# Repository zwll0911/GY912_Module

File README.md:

# 🚁 Industrial AHRS Navigation Module (V5.5)

> **High-Precision Navigation Core for Competition Robotics**

The **Industrial AHRS Navigation Module** is a robust sensor fusion engine built on the **ESP32-S3**. It delivers stable 6-axis orientation (Yaw, Pitch, Roll) via **1 Mbps CAN Bus** and offers **Dual-Mode Telemetry** (USB Serial + Wireless UDP) for real-time monitoring.

---

## 📑 Table of Contents

- [Key Features](#-key-features)
- [System Architecture Overview](#-system-architecture-overview)
- [Sensor Fusion Pipeline (ICM-20948 DMP)](#-sensor-fusion-pipeline-icm-20948-dmp)
- [System Status Indicators](#-system-status-indicators)
- [FreeRTOS Task Architecture](#freertos-task-architecture)
- [Hardware Specifications](#️-hardware-specifications)
- [Quick Start](#-quick-start)
- [Documentation](#-documentation)
- [Project Structure](#-project-structure)

---

## 🚀 Key Features

| Feature | Detail |
| :--- | :--- |
| **DMP Sensor Fusion** | 6-axis fusion offloaded to ICM-20948 DMP using `GAME_ROTATION_VECTOR` at **225Hz** |
| **Wireless UDP** | Low-latency (~20ms) data streaming over WiFi (Broadcast to `192.168.4.255:4210`) |
| **Dual-Mode Dashboard** | Connect via USB (Web Serial) or Wireless (UDP Relay) for real-time visualization |
| **Power Optimized** | Efficient UDP broadcast, WiFi power save enabled, and smart task scheduling |
| **High-Speed CAN** | ESP32-S3 TWAI driver at **1 Mbps** for Robomaster C620/C610 speed controllers |
| **Environment Sensing** | BMP388 via SPI — Altitude (m), Pressure (hPa), Temperature (°C) at 50Hz ODR |
| **Cyberpunk UI** | NAV PANEL v5.4 — Smoothed 3D cube, 30Hz live graphs, tare heading, health stats |

---

## 🧠 System Architecture Overview

```mermaid
flowchart LR
    subgraph Hardware
        IMU["ICM-20948<br/>(DMP)"]
        BARO["BMP388"]
        Bus((CAN Bus<br/>1 Mbps))
        WiFi((WiFi AP<br/>UDP Broadcast))
    end

    subgraph Core1 ["Core 1: taskSensor (P3, 200Hz)"]
        direction TB
        FIFO[Read DMP FIFO]
        Quat["Quaternion"]
        Euler["Euler Angles"]
        BMP[Read BMP388]
        CSV[Build CSV]
    end

    subgraph Core0 ["Core 0"]
        direction TB
        CAN_Task["taskCAN (P2, 50Hz)"]
        LED_Task["taskLED (P1, 10Hz)"]
        Pool_Task["loop() (P1, Idle)"]
    end

    Mutex{{"🔒 Mutex"}}

    IMU -->|SPI 3MHz| FIFO
    FIFO --> Quat --> Euler
    BARO -->|SPI| BMP
    Euler & BMP --> CSV
    Euler --> Mutex
    Mutex --> CAN_Task
    CAN_Task -->|"ID:0x101"| Bus
    CSV -.->|Wireless| WiFi
```

---

## 🌀 Sensor Fusion Pipeline (ICM-20948 DMP)

The module offloads complex sensor fusion math to the ICM-20948's **Digital Motion Processor (DMP)**. This frees up the ESP32-S3 for CAN communication and logic.

1.  **Raw Data**: Accel + Gyro sampled internally at 1125Hz.
2.  **DMP Fusion**: 6-axis Game Rotation Vector algorithm runs on DMP.
3.  **FIFO Read**: ESP32 `taskSensor` reads Quaternion (q0, q1, q2, q3) at 225Hz.
4.  **Euler Conversion**: Quaternion converted to Yaw (-180 to +180), Pitch, Roll.
5.  **Output**: Data written to shared mutex variables and Serial/UDP stream.

---

## 💡 System Status Indicators

The module uses dual WS2812B RGB LEDs to communicate system state.

| LED | Pin | Pattern | Meaning | Technical Detail |
| :--- | :--- | :--- | :--- | :--- |
| **Device Status** | **1** | **Solid Green** | Normal Operation | System running, sensor fusion active |
| **Device Status** | **1** | **Breathing Blue** | WiFi / OTA Active | UDP streaming or OTA update pending |
| **Heartbeat** | **48** | **Purple Blink** (0.5Hz) | CPU Alive | Toggles every 1.5s (10Hz loop) |
| **Error** | **48** | **Solid Red** | DMP Init Failure | Sensor initialization failed. Check wiring. |

### FreeRTOS Task Architecture

The ESP32-S3 dual-core processor runs three dedicated FreeRTOS tasks plus the Arduino `loop()`:

1.  **`taskSensor` (Core 1, P3, 200Hz)**: Reads DMP FIFO, reads BMP388, updates orientation.
2.  **`taskCAN` (Core 0, P2, 50Hz)**: Handles CAN transmission and reception.
3.  **`taskLED` (Core 0, P1, 10Hz)**: Updates status LEDs.
4.  **`loop()` (Core 1, P1)**: Handles OTA updates and low-power sleep when idle.

---

## 🛠️ Hardware Specifications

| Component | Specification |
| :--- | :--- |
| **MCU** | ESP32-S3FH4R2 (Dual Core 240MHz, 4MB Flash, 2MB PSRAM) |
| **IMU** | TDK InvenSense ICM-20948 (9-Axis MEMS) |
| **Barometer** | Bosch BMP388 (Precision Altimeter) |
| **CAN Transceiver** | SN65HVD230 (3.3V Logic) |
| **Power Input** | 5V via USB-C or VIN Pin |
| **Logic Level** | 3.3V |

---

## ⚡ Quick Start

### 1. Hardware Setup (PCB v1.1)
Ensure the module is powered via 5V. The LEDs should light up:
- **Pin 1**: Solid Green (Normal) or Breathing Blue (WiFi).
- **Pin 48**: Blinking Purple (Heartbeat).

### 2. Flash Firmware
Use **PlatformIO** (recommended) or Arduino IDE.
- **PlatformIO**: Open project folder → Click `Upload`.
- **Arduino**: Open `firmware/esp32s3/esp32s3.ino` → Select "ESP32S3 Dev Module" → Upload.

### 3. Calibration
Place the module on a flat, stationary surface for 3 seconds after power-up. The DMP auto-calibrates gyro bias.

### 4. Connect CAN
Hook up `CAN H` and `CAN L` to your Robomaster bus network (**1 Mbps**).

### 5. Launch Dashboard (Dual Mode)
- **Wired:** Open `firmware/index.html` → Click **🔌 USB** → Select Port.
- **Wireless:** Connect to `NAV_MODULE_OTA` WiFi → Run `python firmware/udp_relay.py` → Click **📡 WIFI**.

---

## 📚 Documentation

| Document | Description |
| :--- | :--- |
| 📖 [Hardware & Pinout](docs/HARDWARE.md) | Wiring diagrams, pin maps, Mermaid connection diagram |
| 📡 [CAN Protocol](docs/CAN_PROTOCOL.md) | Message ID 0x101, byte-level packing, decoding math |
| 🏗️ [System Architecture](docs/ARCHITECTURE.md) | FreeRTOS tasks, DMP pipeline, quaternion math, data flow |
| 🖥️ [Web Dashboard](docs/WEB_DASHBOARD.md) | NAV PANEL v5.3 — Dual-mode connect, 3D cube, smoothing |
| 🔩 [PCB Design](docs/PCB_DESIGN.md) | Circuit block diagram and component BOM |
| 📋 [Changelog](CHANGELOG.md) | Full version history (v1.0 → v5.3) |

---

## 📂 Project Structure

```text
.
├── firmware/
│   ├── esp32s3/
│   │   └── esp32s3.ino       # Main firmware (FreeRTOS, DMP, CAN, LED)
│   ├── index.html            # NAV PANEL v5.3 (Web Serial + WebSocket)
│   ├── udp_relay.py          # Python UDP-to-WebSocket Relay
│   ├── chart.js              # Chart.js (bundled for offline use)
│   └── README.md             # Firmware-specific documentation
├── docs/
│   ├── ARCHITECTURE.md       # System architecture & math
│   ├── CAN_PROTOCOL.md       # CAN protocol specification
│   ├── HARDWARE.md           # Pinout & wiring guide
│   ├── WEB_DASHBOARD.md      # Dashboard user guide
│   ├── PCB_DESIGN.md         # PCB design documentation
│   └── dashboard_preview.png # Dashboard screenshot
├── v1/                       # KiCad PCB design files
├── .github/                  # CI workflow
├── LICENSE                   # MIT License
└── README.md                 # This file
```

---

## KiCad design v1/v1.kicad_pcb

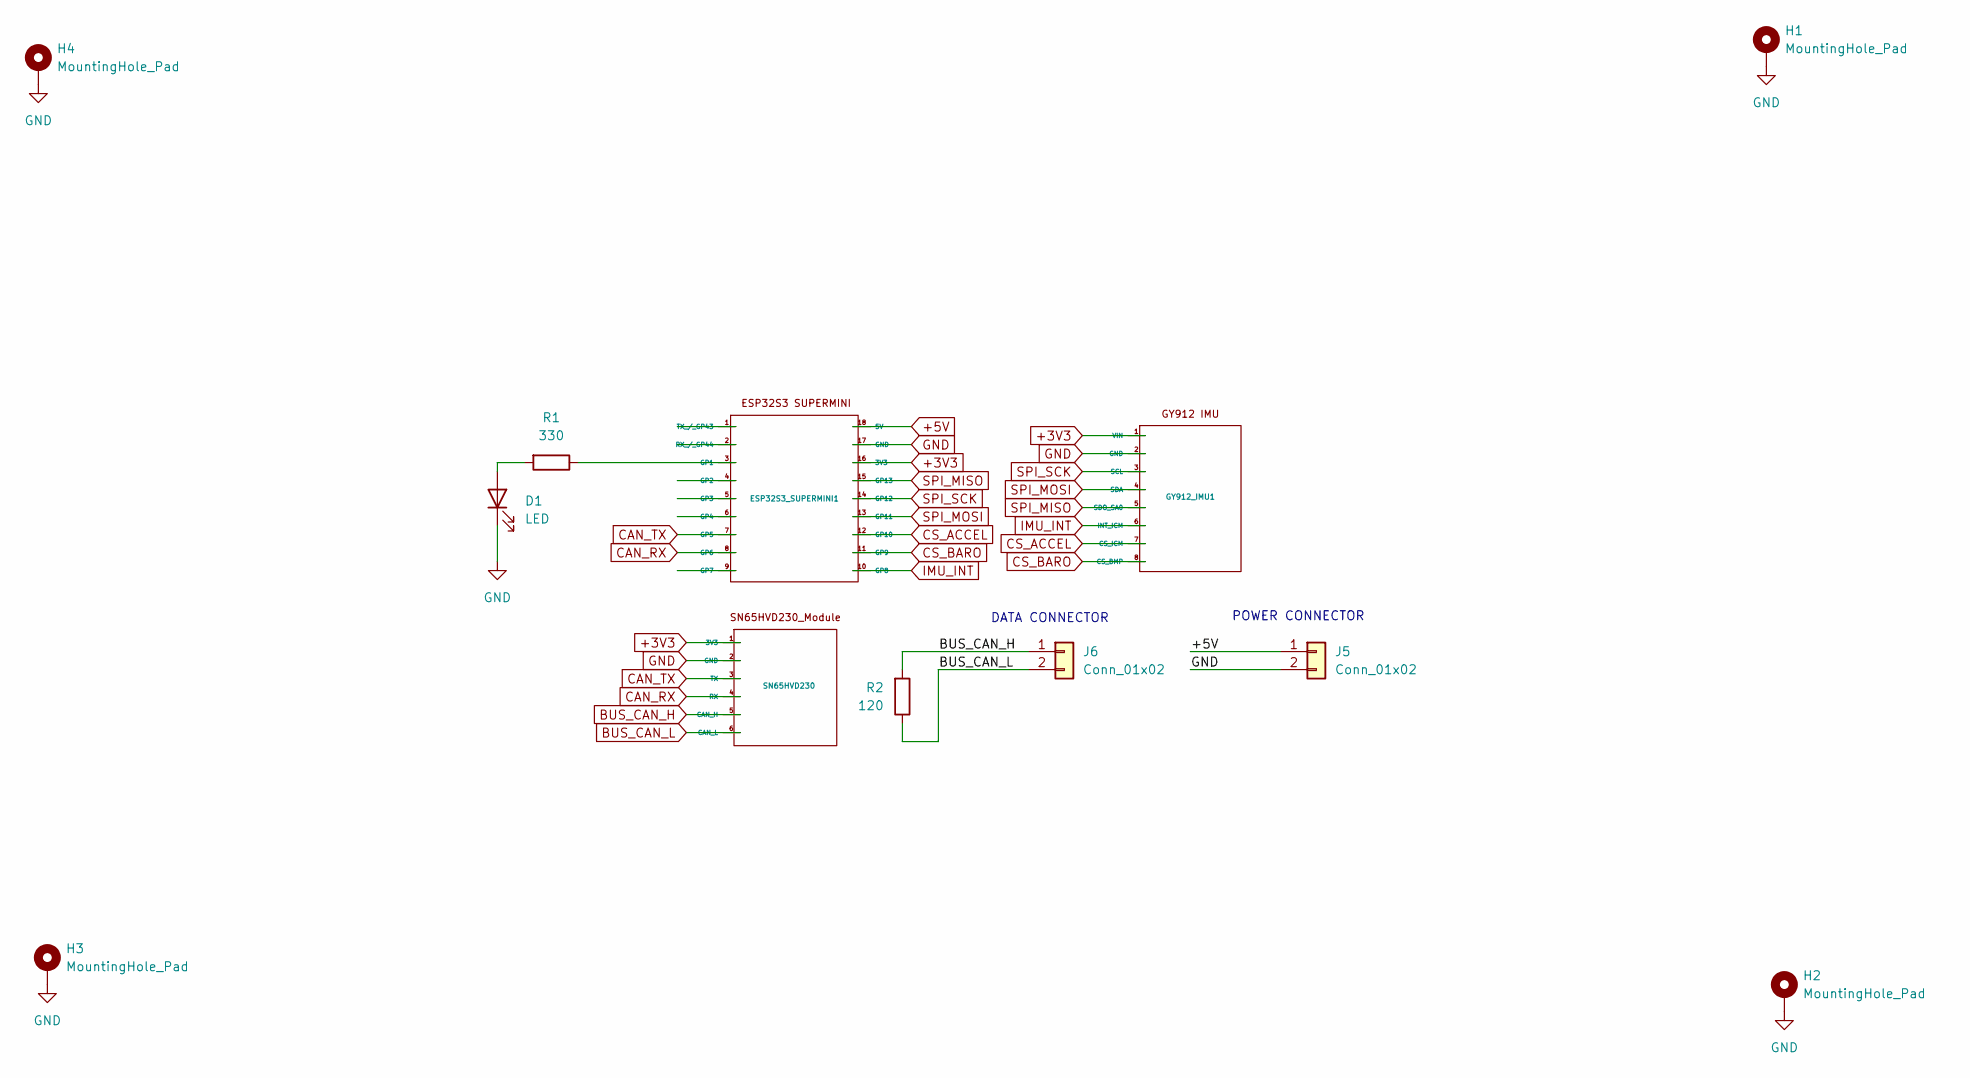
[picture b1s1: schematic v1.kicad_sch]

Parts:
D1: LED; LED_D3.0mm
ESP32S3_SUPERMINI1: ESP32_S3_SuperMini_Footprint
GY912_IMU1: GY-912_IMU_Footprint
H1, H2, H3, H4: MountingHole_Pad; MountingHole_3.2mm_M3_Pad_Via
J5: Conn_01x02; TerminalBlock_Phoenix_MKDS-1,5-2-5.08_1x02_P5.08mm_Horizont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
J6: Conn_01x02; JST_XH_B2B-XH-A_1x02_P2.50mm_Vertical
R1: 330; R_Axial_DIN0207_L6.3mm_D2.5mm_P7.62mm_Horizontal
R2: 120; R_Axial_DIN0207_L6.3mm_D2.5mm_P7.62mm_Horizontal
SN65HVD230: SN65HVD230_Module_Footprint

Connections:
+3V3: ESP32S3_SUPERMINI1.16 (3V3), GY912_IMU1.1 (VIN), SN65HVD230.1 (3V3)
+5V: ESP32S3_SUPERMINI1.18 (5V), J5.1
BUS_CAN_H: J6.1, R2.2, SN65HVD230.5 (CAN_H)
BUS_CAN_L: J6.2, R2.1, SN65HVD230.6 (CAN_L)
CAN_RX: ESP32S3_SUPERMINI1.8 (GP6), SN65HVD230.4 (RX)
CAN_TX: ESP32S3_SUPERMINI1.7 (GP5), SN65HVD230.3 (TX)
CS_ACCEL: ESP32S3_SUPERMINI1.12 (GP10), GY912_IMU1.7 (CS_ICM)
CS_BARO: ESP32S3_SUPERMINI1.11 (GP9), GY912_IMU1.8 (CS_BMP)
GND: D1.1 (K), ESP32S3_SUPERMINI1.17 (GND), GY912_IMU1.2 (GND), H1.1, H2.1, H3.1, H4.1, J5.2, SN65HVD230.2 (GND)
IMU_INT: ESP32S3_SUPERMINI1.10 (GP8), GY912_IMU1.6 (INT_ICM)
unnamed: D1.2 (A), R1.2
unnamed: ESP32S3_SUPERMINI1.3 (GP1), R1.1
SPI_MISO: ESP32S3_SUPERMINI1.15 (GP13), GY912_IMU1.5 (SDO_SA0)
SPI_MOSI: ESP32S3_SUPERMINI1.13 (GP11), GY912_IMU1.4 (SDA)
SPI_SCK: ESP32S3_SUPERMINI1.14 (GP12), GY912_IMU1.3 (SCL)

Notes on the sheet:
DATA CONNECTOR
POWER CONNECTOR

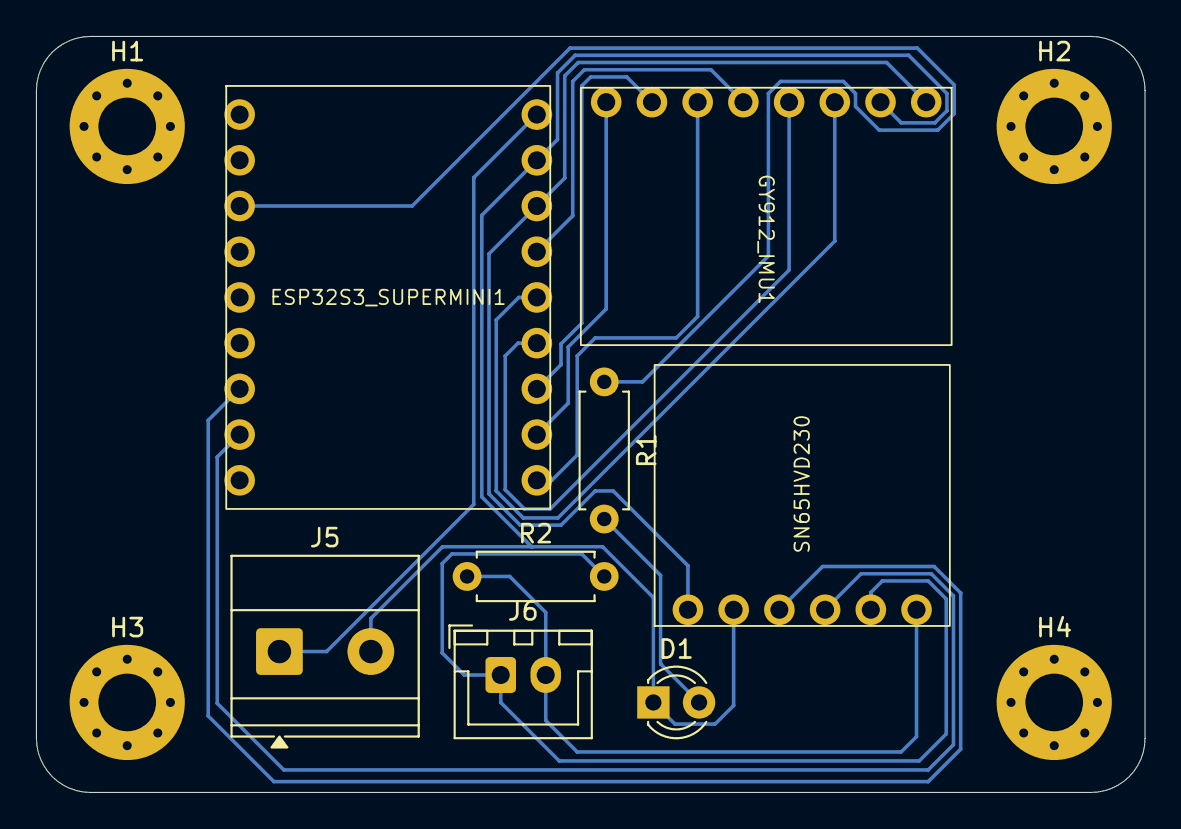
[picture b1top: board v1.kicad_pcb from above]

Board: 2 copper layers, 61.6 x 42.0 mm, 12 parts (0 on the bottom side), 15 nets.

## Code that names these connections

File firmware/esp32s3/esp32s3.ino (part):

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#include <WiFiUdp.h> // UDP low-latency streaming

// --- PINS ---
#define PIN_SPI_SCK 12
#define PIN_SPI_MISO 13
#define PIN_SPI_MOSI 11
#define PIN_CS_ACCEL 10
#define PIN_CS_BARO 9
#define PIN_CAN_TX 5
#define PIN_CAN_RX 6
#define PIN_LED_EXT 1 // Rainbow LED
#define PIN_LED_OB 48 // Blinking Purple LED

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
void setup() {
  Serial.begin(115200);
  pinMode(PIN_CS_ACCEL, OUTPUT);
  digitalWrite(PIN_CS_ACCEL, HIGH);
  pinMode(PIN_CS_BARO, OUTPUT);
  digitalWrite(PIN_CS_BARO, HIGH);

  // Initialize LEDs
  extLED.begin();
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  obLED.begin();
  obLED.setBrightness(50);

  SPI.begin(PIN_SPI_SCK, PIN_SPI_MISO, PIN_SPI_MOSI, -1);
  dataMutex = xSemaphoreCreateMutex();

  // --- 0. Load NVS Settings ---
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                otaEnabled ? "ON" : "OFF");

  // --- 1. Initialize Sensor (DMP) ---
  myICM.begin(PIN_CS_ACCEL, SPI, 3000000);

  bool success = true;
  if (myICM.initializeDMP() != ICM_20948_Stat_Ok) {
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  myICM.resetFIFO();

  // --- 2. Initialize Barometer ---
  if (!bmp.begin_SPI(PIN_CS_BARO, &SPI)) {
    Serial.println("BMP388 Fail");
  } else {
    bmp.setTemperatureOversampling(BMP3_OVERSAMPLING_8X);
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
  // --- 3. Initialize CAN Bus ---
  twai_general_config_t g_config = TWAI_GENERAL_CONFIG_DEFAULT(
      (gpio_num_t)PIN_CAN_TX, (gpio_num_t)PIN_CAN_RX, TWAI_MODE_NORMAL);
  twai_timing_config_t t_config = TWAI_TIMING_CONFIG_1MBITS();
  twai_filter_config_t f_config = TWAI_FILTER_CONFIG_ACCEPT_ALL();

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
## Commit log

2026-02-10 Update README with project overview
2026-02-10 Fix typos and diagram arrows in HARDWARE.md
2026-02-10 Fix Mermaid diagram syntax error (add quotes)
2026-02-10 Refine documentation formatting and visuals
2026-02-10 Add Web Dashboard documentation with live screenshot
2026-02-10 Make dashboard offline - bundle Chart.js locally
2026-02-10 Add .gitignore and MIT LICENSE, remove tracked backups
2026-02-10 Add PCB design documentation with block diagram and BOM
2026-02-10 Add 3D orientation cube to dashboard
2026-02-10 Add simulation mode to dashboard for hardware-free testing
2026-02-10 Add GitHub Actions CI workflow and firmware README
2026-02-10 Update WEB_DASHBOARD.md with 3D Orientation and Simulation Mode docs
2026-02-11 v5.1: DMP sensor fusion, 3-task FreeRTOS, cyberpunk dashboard, updated docs
2026-02-11 docs: comprehensive documentation with full calculations, code refs, and dashboard preview
2026-02-11 v5.2: 12 improvements - mutex optimization, CAN recovery, watchdog, health telemetry, NVS, offline dashboard, reconnect, CSV recorder
2026-02-11 v5.3: drift indicator, bidirectional CAN, OTA, NVS config, altitude smoothing, compass rose, theme toggle, error counters, unit tests
2026-02-11 fix: light theme contrast - darker accent colors, cube face overrides, no text-shadow on values
2026-02-12 Update to v5.4: UDP Streaming & Power Optimization
2026-02-12 Update to v5.5: Documentation & Branding Updates
